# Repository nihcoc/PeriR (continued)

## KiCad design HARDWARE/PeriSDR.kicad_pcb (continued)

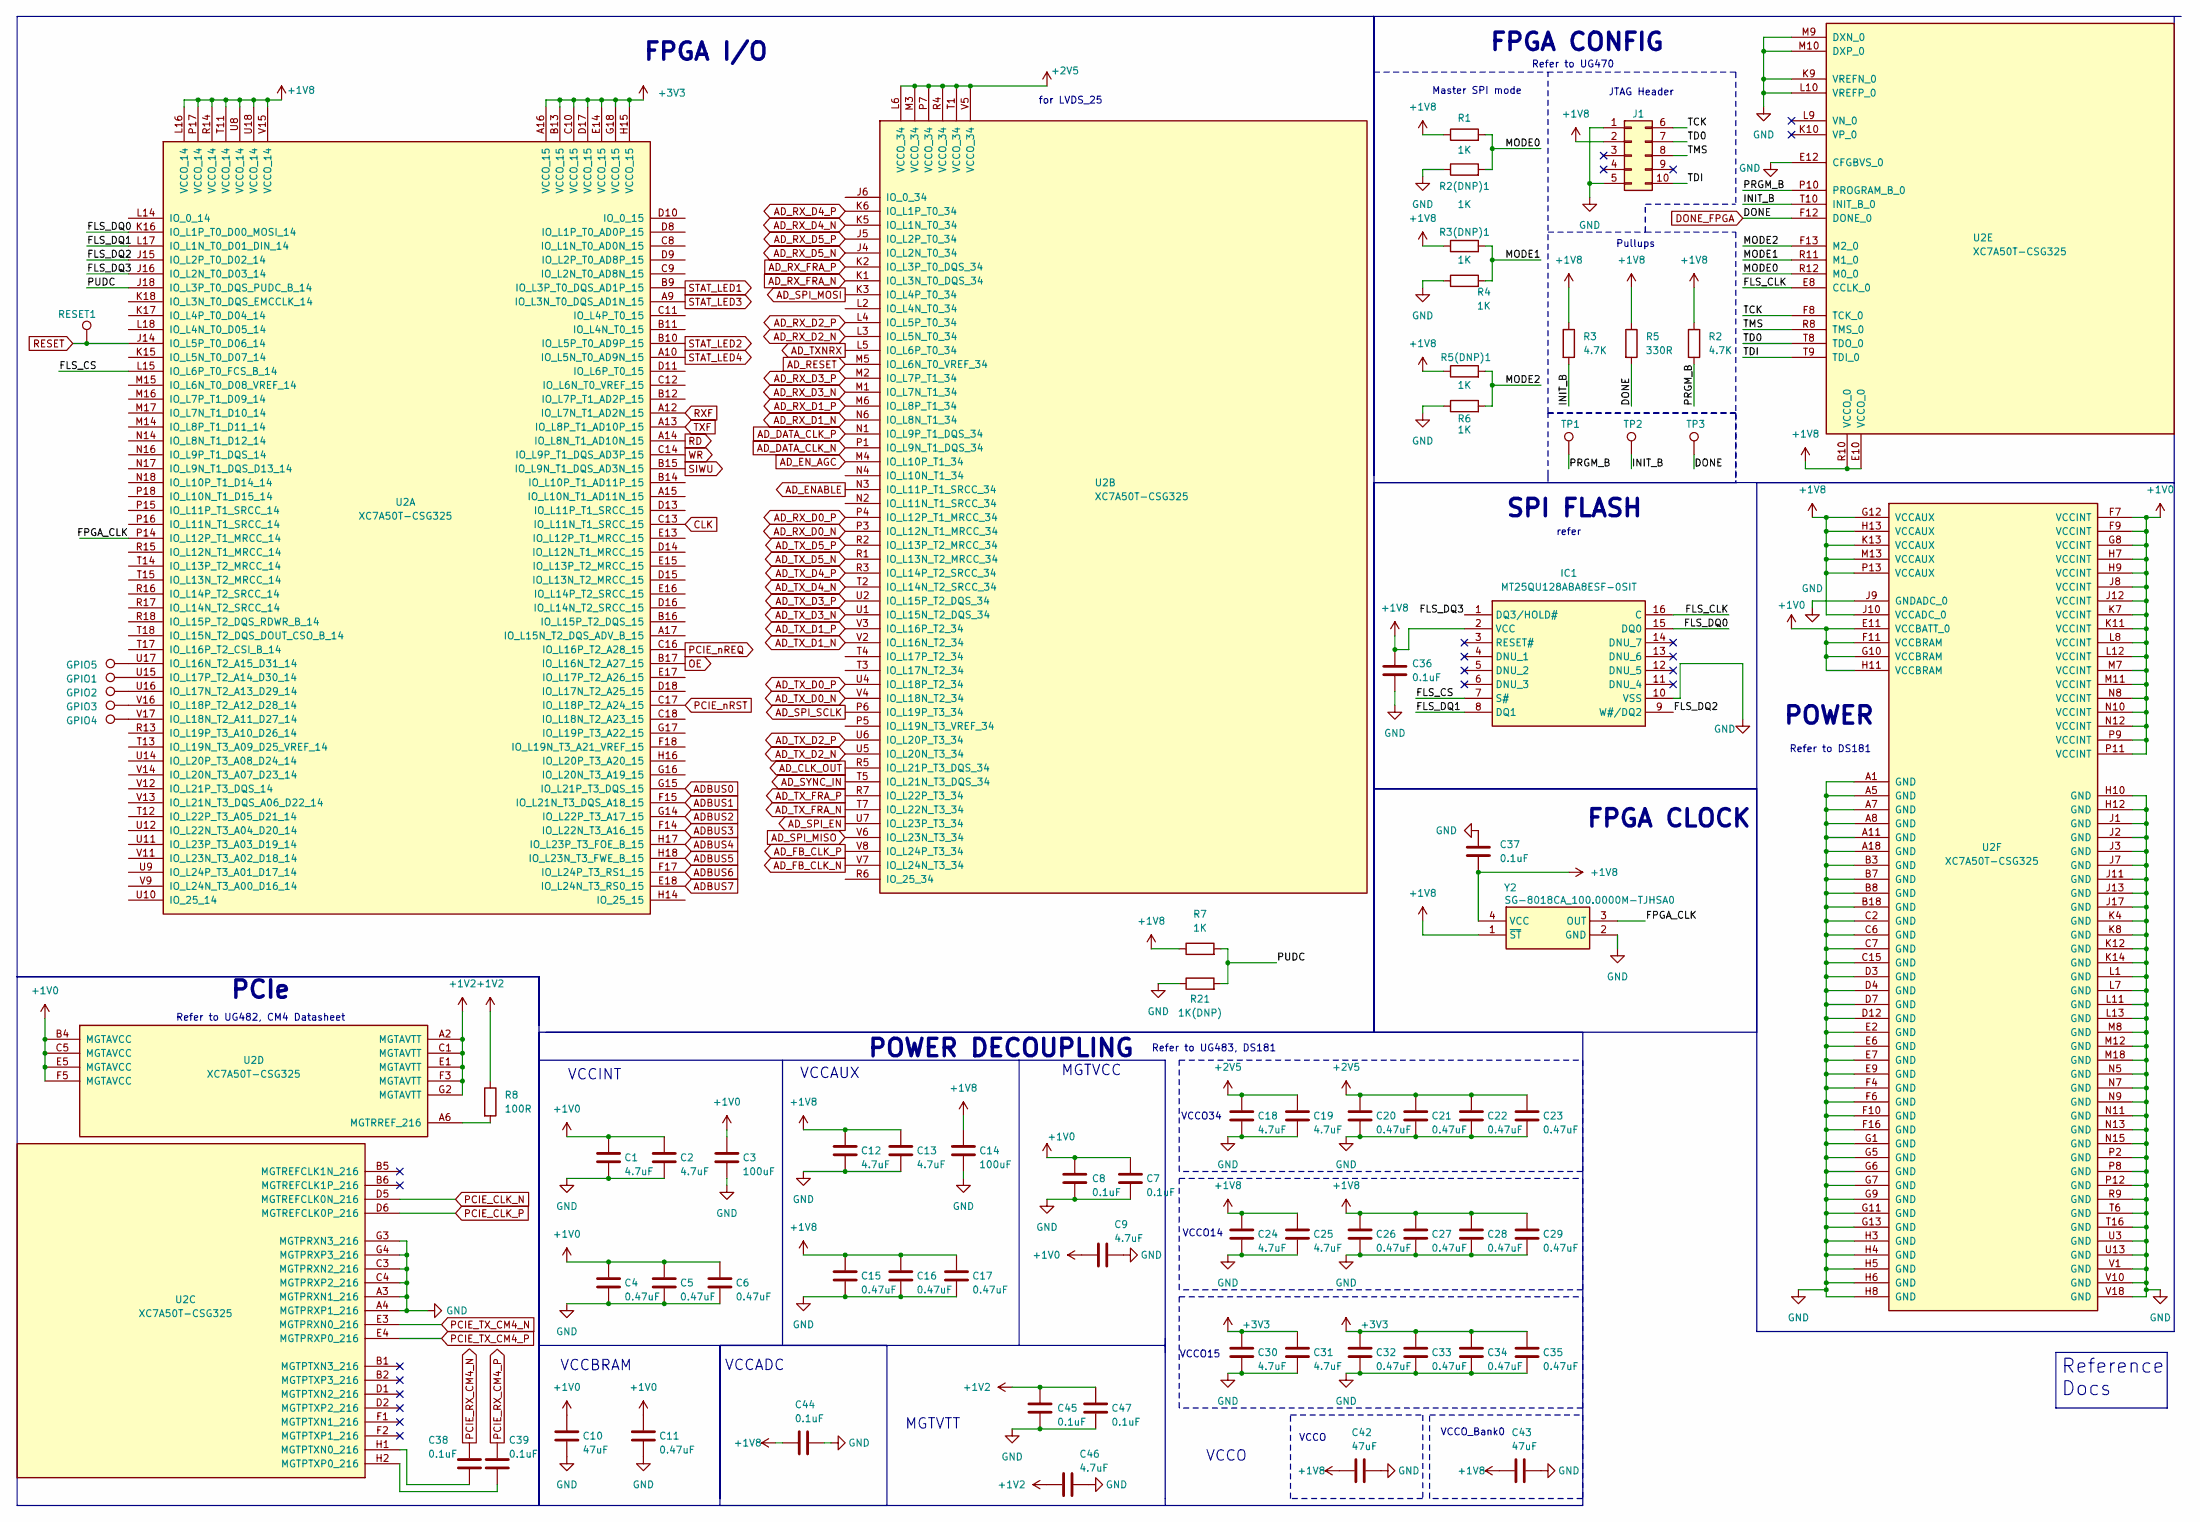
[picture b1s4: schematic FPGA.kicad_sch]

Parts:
C1, C2, C9, C12, C13, C18, C19, C24, C25, C30, C31, C46: 4.7uF; C_0402_1005Metric
C3, C14: 100uF; C_0805_2012Metric
C4, C5, C6, C11, C15, C16, C17, C20, C21, C22, C23, C26, C27, C28, C29, C32, C33, C34, C35: 0.47uF; C_0402_1005Metric
C7, C8, C36, C37, C38, C39, C44, C45, C47: 0.1uF; C_0402_1005Metric
C10, C42, C43: 47uF; C_0603_1608Metric
GPIO1, GPIO2, GPIO3, GPIO4, GPIO5: TestPoint; TestPoint_Pad_1.0x1.0mm
IC1: MT25QU128ABA8ESF-0SIT; SOIC127P1032X265-16N; Mouser Part Number 340-283176-TRAY
J1: Conn_02x05_Top_Bottom; PinHeader_2x05_P2.54mm_Vertical
R1, R2(DNP)1, R3(DNP)1, R4, R5(DNP)1, R6, R7: 1K; R_0402_1005Metric
R2, R3: 4.7K; R_0402_1005Metric
R5: 330R; R_0402_1005Metric
R8: 100R; R_0402_1005Metric
R21: 1K(DNP); R_0402_1005Metric
RESET1: TestPoint; TestPoint_Pad_1.0x1.0mm
TP1, TP2, TP3: TestPoint; TestPoint_Pad_1.0x1.0mm
U2: XC7A50T-CSG325; Xilinx_CSG325
Y2: SG-8018CA_100.0000M-TJHSA0; SG8018CA1000000MTJHSA0; Manufacturer_Part_Number SG-8018CA 100.0000M-TJHSA0

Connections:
+1V0: C1.1, C2.1, C3.1, C4.1, C5.1, C6.1, C7.1, C8.1, C9.1, C10.1, C11.1, U2.B4 (MGTAVCC), U2.C5 (MGTAVCC), U2.E5 (MGTAVCC), U2.E11 (VCCBATT_0), U2.F5 (MGTAVCC), U2.F7 (VCCINT), U2.F9 (VCCINT), U2.F11 (VCCBRAM), U2.G8 (VCCINT), U2.G10 (VCCBRAM), U2.H7 (VCCINT), U2.H9 (VCCINT), U2.H11 (VCCBRAM), U2.J8 (VCCINT), U2.J12 (VCCINT), U2.K7 (VCCINT), U2.K11 (VCCINT), U2.L8 (VCCINT), U2.L12 (VCCINT), U2.M7 (VCCINT), U2.M11 (VCCINT), U2.N8 (VCCINT), U2.N10 (VCCINT), U2.N12 (VCCINT), U2.P9 (VCCINT), U2.P11 (VCCINT); also elsewhere on the board
+1V2: C45.1, C46.1, C47.1, R8.1, U2.A2 (MGTAVTT), U2.C1 (MGTAVTT), U2.E1 (MGTAVTT), U2.F3 (MGTAVTT), U2.G2 (MGTAVTT); also elsewhere on the board
+1V8: C12.1, C13.1, C14.1, C15.1, C16.1, C17.1, C24.1, C25.1, C26.1, C27.1, C28.1, C29.1, C36.1, C37.1, C42.1, C43.1, C44.1, IC1.2 (VCC), J1.2, R1.1, R2.1, R3.1, R3(DNP)1.1, R5.1, R5(DNP)1.1, R7.1, U2.E10 (VCCO_0), U2.G12 (VCCAUX), U2.H13 (VCCAUX), U2.J10 (VCCADC_0), U2.K13 (VCCAUX), U2.L16 (VCCO_14), U2.M13 (VCCAUX), U2.P13 (VCCAUX), U2.P17 (VCCO_14), U2.R10 (VCCO_0), U2.R14 (VCCO_14), U2.T11 (VCCO_14), U2.U8 (VCCO_14), U2.U18 (VCCO_14), U2.V15 (VCCO_14), Y2.1 (~ST), Y2.4 (VCC); also elsewhere on the board
+2V5: C18.1, C19.1, C20.1, C21.1, C22.1, C23.1, U2.L6 (VCCO_34), U2.M3 (VCCO_34), U2.P7 (VCCO_34), U2.R4 (VCCO_34), U2.T1 (VCCO_34), U2.V5 (VCCO_34); also elsewhere on the board
+3V3: C30.1, C31.1, C32.1, C33.1, C34.1, C35.1, U2.A16 (VCCO_15), U2.B13 (VCCO_15), U2.C10 (VCCO_15), U2.D17 (VCCO_15), U2.E14 (VCCO_15), U2.G18 (VCCO_15), U2.H15 (VCCO_15); also elsewhere on the board
/FPGA/FLS_CLK: IC1.16 (C), U2.E8 (CCLK_0)
/FPGA/FLS_CS: IC1.7 (S#), U2.L15 (IO_L6P_T0_FCS_B_14)
/FPGA/FLS_DQ0: IC1.15 (DQ0), U2.K16 (IO_L1P_T0_D00_MOSI_14)
/FPGA/FLS_DQ1: IC1.8 (DQ1), U2.L17 (IO_L1N_T0_D01_DIN_14)
/FPGA/FLS_DQ2: IC1.9 (W#/DQ2), U2.J15 (IO_L2P_T0_D02_14)
/FPGA/FLS_DQ3: IC1.1 (DQ3/HOLD#), U2.J16 (IO_L2N_T0_D03_14)
/FPGA/FPGA_CLK: U2.P14 (IO_L12P_T1_MRCC_14), Y2.3 (OUT)
/FPGA/INIT_B: R3.2, TP2.1 (1_1), U2.T10 (INIT_B_0)
/FPGA/MODE0: R1.2, R2(DNP)1.2, U2.R12 (M0_0)
/FPGA/MODE1: R3(DNP)1.2, R4.2, U2.R11 (M1_0)
/FPGA/MODE2: R5(DNP)1.2, R6.2, U2.F13 (M2_0)
/FPGA/PRGM_B: R2.2, TP1.1 (1_1), U2.P10 (PROGRAM_B_0)
/FPGA/PUDC: R7.2, R21.2, U2.J18 (IO_L3P_T0_DQS_PUDC_B_14)
/FPGA/TCK: J1.6, U2.F8 (TCK_0)
/FPGA/TD0: J1.7, U2.T8 (TDO_0)
/FPGA/TDI: J1.10, U2.T9 (TDI_0)
/FPGA/TMS: J1.8, U2.R8 (TMS_0)
ADBUS0: U2.G15 (IO_L21P_T3_DQS_15); also elsewhere on the board
ADBUS1: U2.F15 (IO_L21N_T3_DQS_A18_15); also elsewhere on the board
ADBUS2: U2.G14 (IO_L22P_T3_A17_15); also elsewhere on the board
ADBUS3: U2.F14 (IO_L22N_T3_A16_15); also elsewhere on the board
ADBUS4: U2.H17 (IO_L23P_T3_FOE_B_15); also elsewhere on the board
ADBUS5: U2.H18 (IO_L23N_T3_FWE_B_15); also elsewhere on the board
ADBUS6: U2.F17 (IO_L24P_T3_RS1_15); also elsewhere on the board
ADBUS7: U2.E18 (IO_L24N_T3_RS0_15); also elsewhere on the board
AD_CLK_OUT: U2.R5 (IO_L21P_T3_DQS_34); also elsewhere on the board
AD_DATA_CLK_N: U2.P1 (IO_L9N_T1_DQS_34); also elsewhere on the board
AD_DATA_CLK_P: U2.N1 (IO_L9P_T1_DQS_34); also elsewhere on the board
AD_ENABLE: U2.N3 (IO_L11P_T1_SRCC_34); also elsewhere on the board
AD_EN_AGC: U2.M4 (IO_L10P_T1_34); also elsewhere on the board
AD_FB_CLK_N: U2.V7 (IO_L24N_T3_34); also elsewhere on the board
AD_FB_CLK_P: U2.V8 (IO_L24P_T3_34); also elsewhere on the board
AD_RESET: U2.M5 (IO_L6N_T0_VREF_34); also elsewhere on the board
AD_RX_D0_N: U2.P3 (IO_L12N_T1_MRCC_34); also elsewhere on the board
AD_RX_D0_P: U2.P4 (IO_L12P_T1_MRCC_34); also elsewhere on the board
AD_RX_D1_N: U2.N6 (IO_L8N_T1_34); also elsewhere on the board
AD_RX_D1_P: U2.M6 (IO_L8P_T1_34); also elsewhere on the board
AD_RX_D2_N: U2.L3 (IO_L5N_T0_34); also elsewhere on the board
AD_RX_D2_P: U2.L4 (IO_L5P_T0_34); also elsewhere on the board
AD_RX_D3_N: U2.M1 (IO_L7N_T1_34); also elsewhere on the board
AD_RX_D3_P: U2.M2 (IO_L7P_T1_34); also elsewhere on the board
AD_RX_D4_N: U2.K5 (IO_L1N_T0_34); also elsewhere on the board
AD_RX_D4_P: U2.K6 (IO_L1P_T0_34); also elsewhere on the board
AD_RX_D5_N: U2.J4 (IO_L2N_T0_34); also elsewhere on the board
AD_RX_D5_P: U2.J5 (IO_L2P_T0_34); also elsewhere on the board
AD_RX_FRA_N: U2.K1 (IO_L3N_T0_DQS_34); also elsewhere on the board
AD_RX_FRA_P: U2.K2 (IO_L3P_T0_DQS_34); also elsewhere on the board
AD_SPI_EN: U2.U7 (IO_L23P_T3_34); also elsewhere on the board
AD_SPI_MISO: U2.V6 (IO_L23N_T3_34); also elsewhere on the board
AD_SPI_MOSI: U2.K3 (IO_L4P_T0_34); also elsewhere on the board
AD_SPI_SCLK: U2.P6 (IO_L19P_T3_34); also elsewhere on the board
AD_SYNC_IN: U2.T5 (IO_L21N_T3_DQS_34); also elsewhere on the board
AD_TXNRX: U2.L5 (IO_L6P_T0_34); also elsewhere on the board
AD_TX_D0_N: U2.V4 (IO_L18N_T2_34); also elsewhere on the board
AD_TX_D0_P: U2.U4 (IO_L18P_T2_34); also elsewhere on the board
AD_TX_D1_N: U2.V2 (IO_L16N_T2_34); also elsewhere on the board
AD_TX_D1_P: U2.V3 (IO_L16P_T2_34); also elsewhere on the board
AD_TX_D2_N: U2.U5 (IO_L20N_T3_34); also elsewhere on the board
AD_TX_D2_P: U2.U6 (IO_L20P_T3_34); also elsewhere on the board
AD_TX_D3_N: U2.U1 (IO_L15N_T2_DQS_34); also elsewhere on the board
AD_TX_D3_P: U2.U2 (IO_L15P_T2_DQS_34); also elsewhere on the board
AD_TX_D4_N: U2.T2 (IO_L14N_T2_SRCC_34); also elsewhere on the board
AD_TX_D4_P: U2.R3 (IO_L14P_T2_SRCC_34); also elsewhere on the board
AD_TX_D5_N: U2.R1 (IO_L13N_T2_MRCC_34); also elsewhere on the board
AD_TX_D5_P: U2.R2 (IO_L13P_T2_MRCC_34); also elsewhere on the board
AD_TX_FRA_N: U2.T7 (IO_L22N_T3_34); also elsewhere on the board
AD_TX_FRA_P: U2.R7 (IO_L22P_T3_34); also elsewhere on the board
CLK: U2.C13 (IO_L11N_T1_SRCC_15); also elsewhere on the board
DONE_FPGA: R5.2, TP3.1 (1_1), U2.F12 (DONE_0); also elsewhere on the board
GND: C1.2, C2.2, C3.2, C4.2, C5.2, C6.2, C7.2, C8.2, C9.2, C10.2, C11.2, C12.2, C13.2, C14.2, C15.2, C16.2, C17.2, C18.2, C19.2, C20.2, C21.2, C22.2, C23.2, C24.2, C25.2, C26.2, C27.2, C28.2, C29.2, C30.2, C31.2, C32.2, C33.2, C34.2, C35.2, C36.2, C37.2, C42.2, C43.2, C44.2, C45.2, C46.2, C47.2, IC1.10 (VSS), J1.1, J1.5, R2(DNP)1.1, R4.1, R6.1, R21.1, U2.A1 (GND), U2.A3 (MGTPRXN1_216), U2.A4 (MGTPRXP1_216), U2.A5 (GND), U2.A7 (GND), U2.A8 (GND), U2.A11 (GND), U2.A18 (GND), U2.B3 (GND), U2.B7 (GND), U2.B8 (GND), U2.B18 (GND), U2.C2 (GND), U2.C3 (MGTPRXN2_216), U2.C4 (MGTPRXP2_216), U2.C6 (GND), U2.C7 (GND), U2.C15 (GND), U2.D3 (GND), U2.D4 (GND), U2.D7 (GND), U2.D12 (GND), U2.E2 (GND), U2.E6 (GND), U2.E7 (GND), U2.E9 (GND), U2.E12 (CFGBVS_0), U2.F4 (GND), U2.F6 (GND), U2.F10 (GND), U2.F16 (GND), U2.G1 (GND), U2.G3 (MGTPRXN3_216), U2.G4 (MGTPRXP3_216), U2.G5 (GND), U2.G6 (GND), U2.G7 (GND), U2.G9 (GND), U2.G11 (GND), U2.G13 (GND), U2.H3 (GND), U2.H4 (GND), U2.H5 (GND), U2.H6 (GND), U2.H8 (GND), U2.H10 (GND), U2.H12 (GND), U2.J1 (GND), U2.J2 (GND), U2.J3 (GND), U2.J7 (GND), U2.J9 (GNDADC_0), U2.J11 (GND), U2.J13 (GND), U2.J17 (GND), U2.K4 (GND), U2.K8 (GND), U2.K9 (VREFN_0), U2.K12 (GND), U2.K14 (GND), U2.L1 (GND), U2.L7 (GND), U2.L10 (VREFP_0), U2.L11 (GND), U2.L13 (GND), U2.M8 (GND), U2.M9 (DXN_0), U2.M10 (DXP_0), U2.M12 (GND), U2.M18 (GND), U2.N5 (GND), U2.N7 (GND), U2.N9 (GND), U2.N11 (GND), U2.N13 (GND), U2.N15 (GND), U2.P2 (GND), U2.P8 (GND), U2.P12 (GND), U2.R9 (GND), U2.T6 (GND), U2.T16 (GND), U2.U3 (GND), U2.U13 (GND), U2.V1 (GND), U2.V10 (GND), U2.V18 (GND), Y2.2 (GND); also elsewhere on the board
unnamed: GPIO5.1 (1_1), U2.U17 (IO_L16N_T2_A15_D31_14)
unnamed: GPIO2.1 (1_1), U2.U16 (IO_L17N_T2_A13_D29_14)
unnamed: GPIO1.1 (1_1), U2.U15 (IO_L17P_T2_A14_D30_14)
unnamed: GPIO4.1 (1_1), U2.V17 (IO_L18N_T2_A11_D27_14)
unnamed: GPIO3.1 (1_1), U2.V16 (IO_L18P_T2_A12_D28_14)
unnamed: C38.1, U2.H1 (MGTPTXN0_216)
unnamed: C39.1, U2.H2 (MGTPTXP0_216)
unnamed: R8.2, U2.A6 (MGTRREF_216)
OE: U2.B17 (IO_L16N_T2_A27_15); also elsewhere on the board
PCIE_CLK_N: U2.D5 (MGTREFCLK0N_216); also elsewhere on the board
PCIE_CLK_P: U2.D6 (MGTREFCLK0P_216); also elsewhere on the board
PCIE_RX_CM4_N: C38.2; also elsewhere on the board
PCIE_RX_CM4_P: C39.2; also elsewhere on the board
PCIE_TX_CM4_N: U2.E3 (MGTPRXN0_216); also elsewhere on the board
PCIE_TX_CM4_P: U2.E4 (MGTPRXP0_216); also elsewhere on the board
PCIE_nREQ: U2.C16 (IO_L16P_T2_A28_15); also elsewhere on the board
PCIE_nRST: U2.C17 (IO_L18P_T2_A24_15); also elsewhere on the board
RD: U2.A14 (IO_L8N_T1_AD10N_15); also elsewhere on the board
RESET: RESET1.1 (1_1), U2.J14 (IO_L5P_T0_D06_14)
RXF: U2.A12 (IO_L7N_T1_AD2N_15); also elsewhere on the board
SIWU: U2.B15 (IO_L9N_T1_DQS_AD3N_15); also elsewhere on the board
STAT_LED1: U2.B9 (IO_L3P_T0_DQS_AD1P_15); also elsewhere on the board
STAT_LED2: U2.B10 (IO_L5P_T0_AD9P_15); also elsewhere on the board
STAT_LED3: U2.A9 (IO_L3N_T0_DQS_AD1N_15); also elsewhere on the board
STAT_LED4: U2.A10 (IO_L5N_T0_AD9N_15); also elsewhere on the board
TXF: U2.A13 (IO_L8P_T1_AD10P_15); also elsewhere on the board
WR: U2.C14 (IO_L9P_T1_DQS_AD3P_15); also elsewhere on the board

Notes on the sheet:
VCCO34
Refer to UG470
VCCBRAM
POWER
FPGA CONFIG
FPGA CLOCK
PCIe
Refer to DS181
VCCO
VCCO
MGTVTT
for LVDS_25
Refer to UG482, CM4 Datasheet
VCCAUX
JTAG Header
MGTVCC
VCCINT
Pullups
VCCADC
Master SPI mode
FPGA I/O
POWER DECOUPLING
VCCO14
Refer to UG483, DS181
refer
SPI FLASH
VCCO15
VCCO_Bank0
Reference Docs

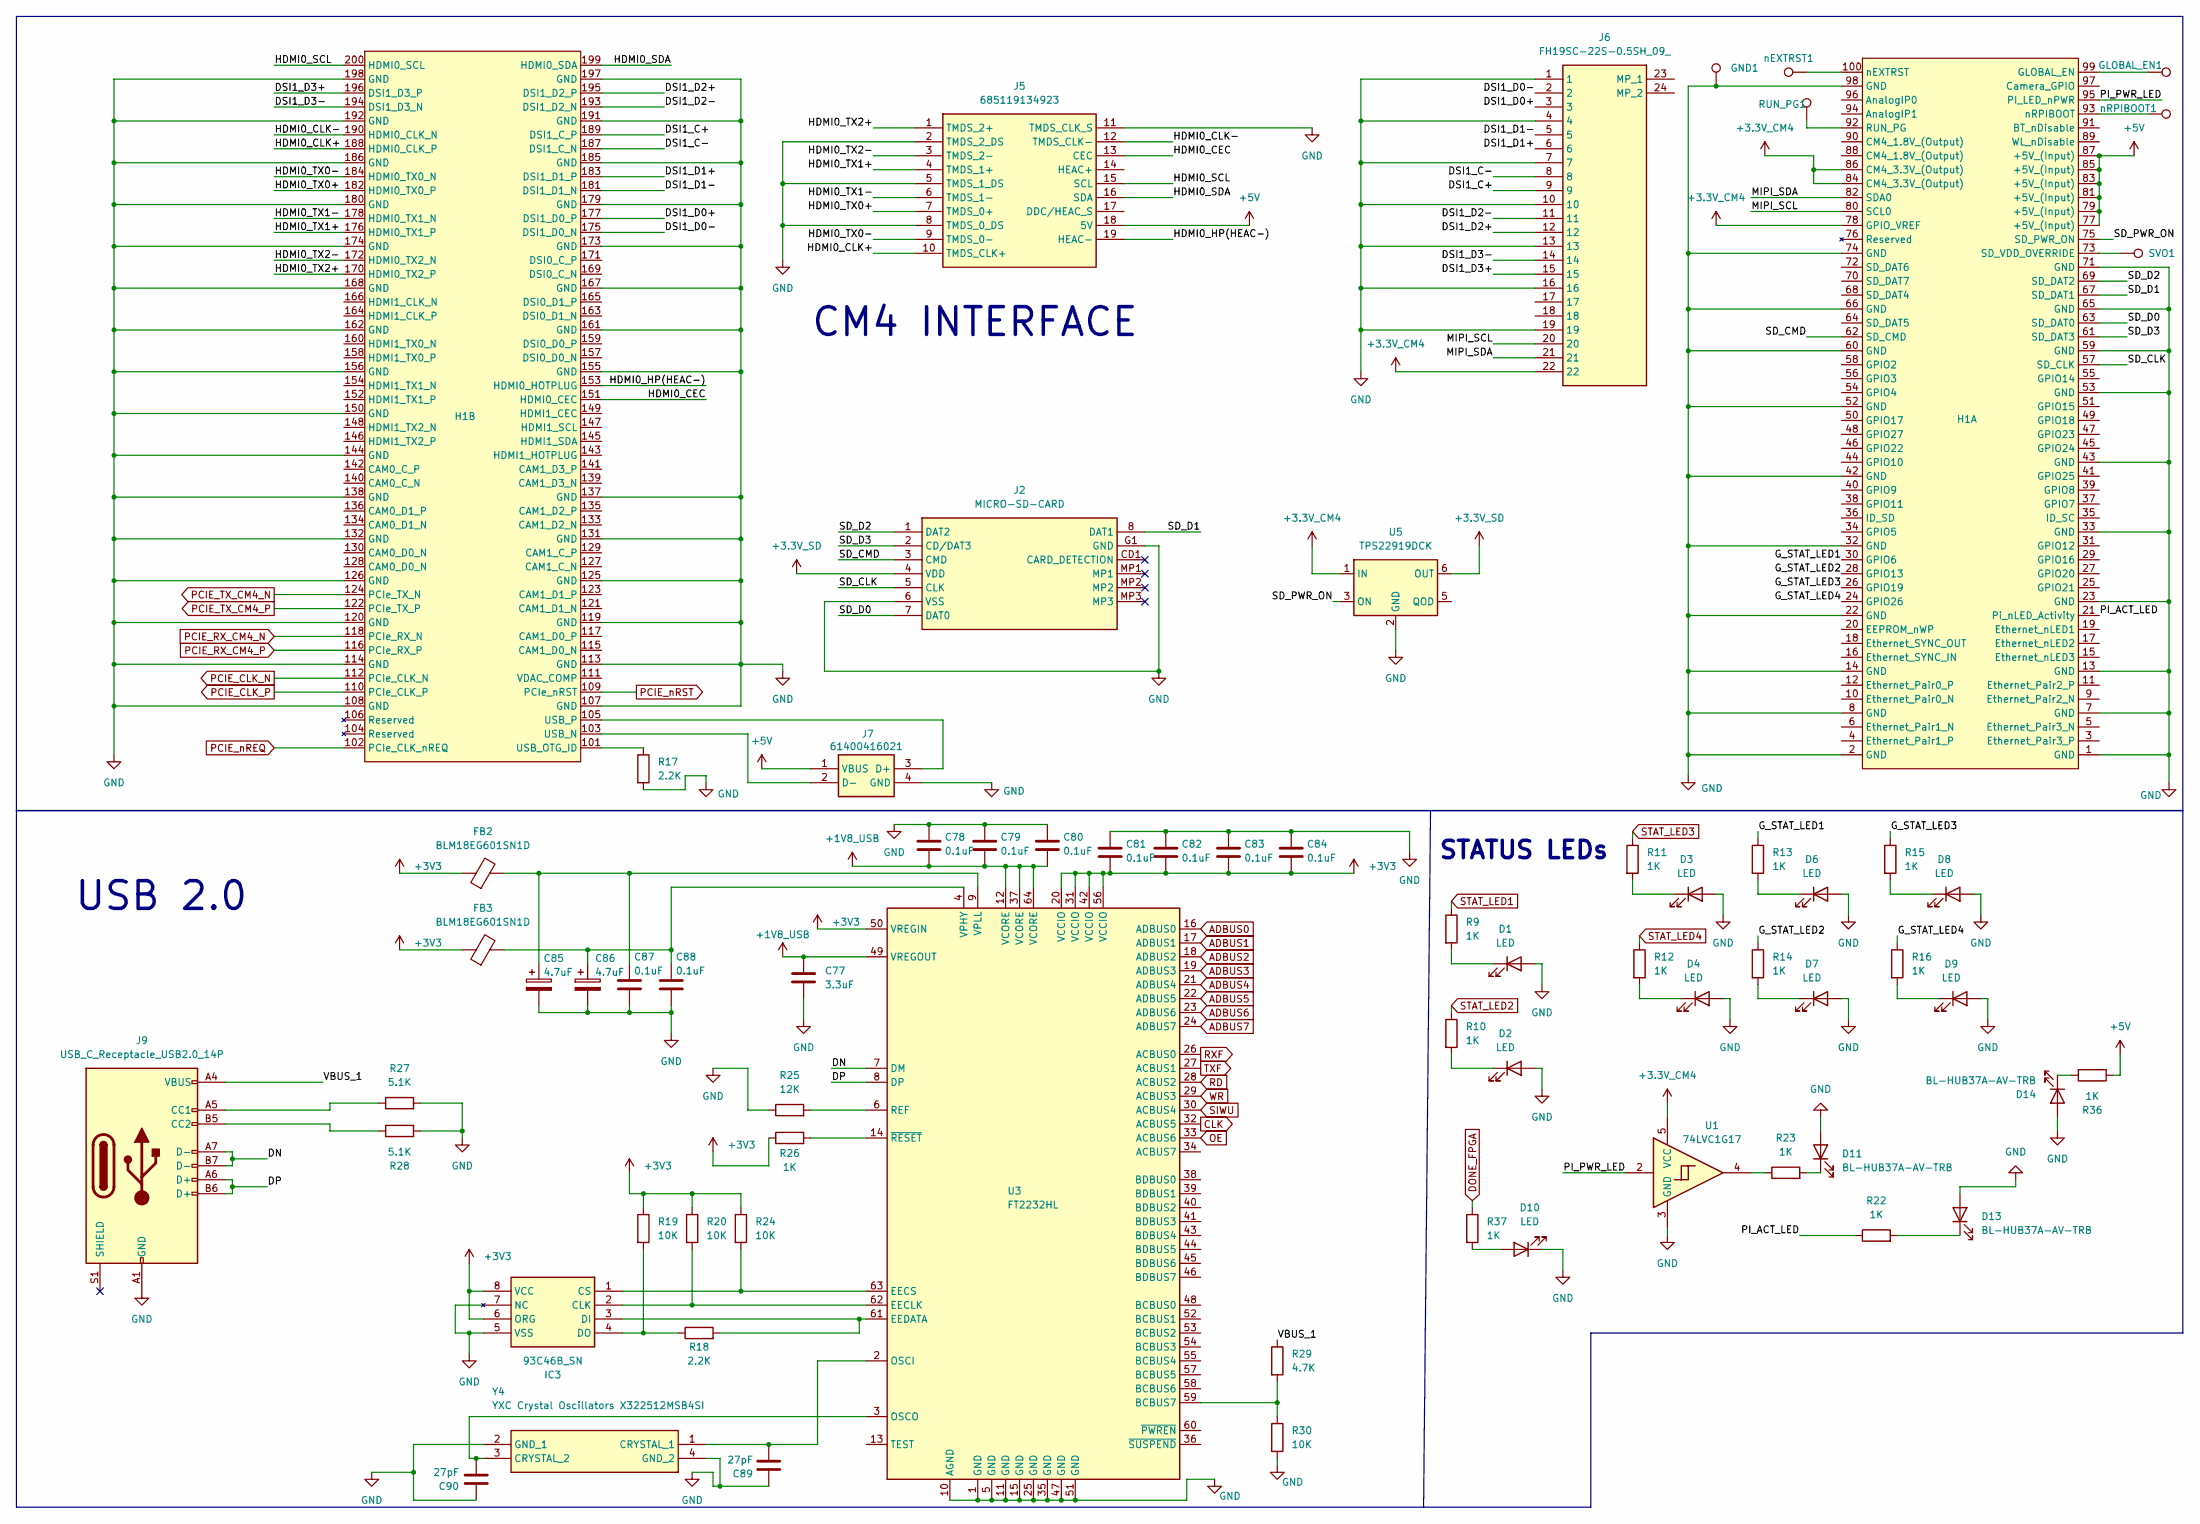
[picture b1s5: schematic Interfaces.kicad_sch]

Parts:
C77: 3.3uF; C_0603_1608Metric
C78, C79, C80, C81, C82, C83, C84, C87, C88: 0.1uF; C_0402_1005Metric
C85, C86: 4.7uF; C_0402_1005Metric
C89, C90: 27pF; C_0201_0603Metric
D1, D2, D3, D4, D6, D7, D8, D9, D10: LED; LED_0402_1005Metric
D11, D13, D14: BL-HUB37A-AV-TRB; LED_0402_1005Metric
FB2, FB3: BLM18EG601SN1D; L_0603_1608Metric
GLOBAL_EN1: TestPoint; TestPoint_Pad_1.0x1.0mm
GND1: TestPoint; TestPoint_Pad_1.0x1.0mm
H1: RaspberryPi-CM4-Module-Pad
IC3: 93C46B_SN; SOIC127P600X175-8N; Manufacturer_Part_Number 93C46B/SN; Mouser Part Number 579-93C46B/SN
J2: MICRO-SD-CARD; MICROSDCARD; Manufacturer_Part_Number MICRO-SD-CARD; Mouser Part Number N/A
J5: 685119134923; Mouser Part Number 710-685119134923
J6: FH19SC-22S-0.5SH_09_; FH19SC22S05SH09; Mouser Part Number 798-FH19SC22S05SH09
J7: 61400416021; USB-2.0-TYPE-A; Mouser Part Number 710-61400416021
J9: USB_C_Receptacle_USB2.0_14P; USB_C_Receptacle_JAE_DX07S016JA1R1500
R9, R10, R11, R12, R13, R14, R15, R16, R22, R23, R26, R36, R37: 1K; R_0402_1005Metric
R17, R18: 2.2K; R_0402_1005Metric
R19, R20, R24, R30: 10K; R_0402_1005Metric
R25: 12K; R_0402_1005Metric
R27, R28: 5.1K; R_0402_1005Metric
R29: 4.7K; R_0402_1005Metric
RUN_PG1: TestPoint; TestPoint_Pad_1.0x1.0mm
SVO1: TestPoint; TestPoint_Pad_1.0x1.0mm
U1: 74LVC1G17; SOT-23-5
U3: FT2232HL; LQFP-64_10x10mm_P0.5mm
U5: TPS22919DCK; SOT-363_SC-70-6
Y4: YXC Crystal Oscillators X322512MSB4SI; FA128400000MF20XK; Mouser Part Number 732-FA-12840MF20X-K
nEXTRST1: TestPoint; TestPoint_Pad_1.0x1.0mm
nRPIBOOT1: TestPoint; TestPoint_Pad_1.0x1.0mm

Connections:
+1V8_USB: C77.1, C78.2, C79.2, C80.2, U3.12 (VCORE), U3.37 (VCORE), U3.49 (VREGOUT), U3.64 (VCORE)
+3.3V_CM4: H1.78 (GPIO_VREF), H1.84 (CM4_3.3V_(Output)), H1.86 (CM4_3.3V_(Output)), J6.22, U1.5 (VCC), U5.1 (IN)
+3.3V_SD: J2.4 (VDD), U5.6 (OUT)
+3V3: C81.2, C82.2, C83.2, C84.2, FB2.1, FB3.1, IC3.6 (ORG), IC3.8 (VCC), R19.1, R20.1, R24.1, R26.1, U3.20 (VCCIO), U3.31 (VCCIO), U3.42 (VCCIO), U3.50 (VREGIN), U3.56 (VCCIO); also elsewhere on the board
+5V: H1.77 (+5V_(Input)), H1.79 (+5V_(Input)), H1.81 (+5V_(Input)), H1.83 (+5V_(Input)), H1.85 (+5V_(Input)), H1.87 (+5V_(Input)), J5.18 (5V), J7.1 (VBUS), R36.1; also elsewhere on the board
/Interfaces/DN: J9.A7 (D-), J9.B7 (D-), U3.7 (DM)
/Interfaces/DP: J9.A6 (D+), J9.B6 (D+), U3.8 (DP)
/Interfaces/DSI1_C+: H1.189 (DSI1_C_P), J6.9
/Interfaces/DSI1_C-: H1.187 (DSI1_C_N), J6.8
/Interfaces/DSI1_D0+: H1.177 (DSI1_D0_P), J6.3
/Interfaces/DSI1_D0-: H1.175 (DSI1_D0_N), J6.2
/Interfaces/DSI1_D1+: H1.183 (DSI1_D1_P), J6.6
/Interfaces/DSI1_D1-: H1.181 (DSI1_D1_N), J6.5
/Interfaces/DSI1_D2+: H1.195 (DSI1_D2_P), J6.12
/Interfaces/DSI1_D2-: H1.193 (DSI1_D2_N), J6.11
/Interfaces/DSI1_D3+: H1.196 (DSI1_D3_P), J6.15
/Interfaces/DSI1_D3-: H1.194 (DSI1_D3_N), J6.14
/Interfaces/G_STAT_LED1: H1.30 (GPIO6), R13.1
/Interfaces/G_STAT_LED2: H1.28 (GPIO13), R14.1
/Interfaces/G_STAT_LED3: H1.26 (GPIO19), R15.1
/Interfaces/G_STAT_LED4: H1.24 (GPIO26), R16.1
/Interfaces/HDMI0_CEC: H1.151 (HDMI0_CEC), J5.13 (CEC)
/Interfaces/HDMI0_CLK+: H1.188 (HDMI0_CLK_P), J5.10 (TMDS_CLK+)
/Interfaces/HDMI0_CLK-: H1.190 (HDMI0_CLK_N), J5.12 (TMDS_CLK-)
/Interfaces/HDMI0_HP(HEAC-): H1.153 (HDMI0_HOTPLUG), J5.19 (HEAC-)
/Interfaces/HDMI0_SCL: H1.200 (HDMI0_SCL), J5.15 (SCL)
/Interfaces/HDMI0_SDA: H1.199 (HDMI0_SDA), J5.16 (SDA)
/Interfaces/HDMI0_TX0+: H1.182 (HDMI0_TX0_P), J5.7 (TMDS_0+)
/Interfaces/HDMI0_TX0-: H1.184 (HDMI0_TX0_N), J5.9 (TMDS_0-)
/Interfaces/HDMI0_TX1+: H1.176 (HDMI0_TX1_P), J5.4 (TMDS_1+)
/Interfaces/HDMI0_TX1-: H1.178 (HDMI0_TX1_N), J5.6 (TMDS_1-)
/Interfaces/HDMI0_TX2+: H1.170 (HDMI0_TX2_P), J5.1 (TMDS_2+)
/Interfaces/HDMI0_TX2-: H1.172 (HDMI0_TX2_N), J5.3 (TMDS_2-)
/Interfaces/MIPI_SCL: H1.80 (SCL0), J6.20
/Interfaces/MIPI_SDA: H1.82 (SDA0), J6.21
/Interfaces/PI_ACT_LED: H1.21 (Pi_nLED_Activity), R22.1
/Interfaces/PI_PWR_LED: H1.95 (PI_LED_nPWR), U1.2
/Interfaces/SD_CLK: H1.57 (SD_CLK), J2.5 (CLK)
/Interfaces/SD_CMD: H1.62 (SD_CMD), J2.3 (CMD)
/Interfaces/SD_D0: H1.63 (SD_DAT0), J2.7 (DAT0)
/Interfaces/SD_D1: H1.67 (SD_DAT1), J2.8 (DAT1)
/Interfaces/SD_D2: H1.69 (SD_DAT2), J2.1 (DAT2)
/Interfaces/SD_D3: H1.61 (SD_DAT3), J2.2 (CD/DAT3)
/Interfaces/SD_PWR_ON: H1.75 (SD_PWR_ON), U5.3 (ON)
/Interfaces/VBUS_1: J9.A4 (VBUS), J9.A9 (VBUS), J9.B4 (VBUS), J9.B9 (VBUS), R29.1
ADBUS0: U3.16 (ADBUS0); also elsewhere on the board
ADBUS1: U3.17 (ADBUS1); also elsewhere on the board
ADBUS2: U3.18 (ADBUS2); also elsewhere on the board
ADBUS3: U3.19 (ADBUS3); also elsewhere on the board
ADBUS4: U3.21 (ADBUS4); also elsewhere on the board
ADBUS5: U3.22 (ADBUS5); also elsewhere on the board
ADBUS6: U3.23 (ADBUS6); also elsewhere on the board
ADBUS7: U3.24 (ADBUS7); also elsewhere on the board
CLK: U3.32 (ACBUS5); also elsewhere on the board
DONE_FPGA: R37.1; also elsewhere on the board
GND: C77.2, C78.1, C79.1, C80.1, C81.1, C82.1, C83.1, C84.1, C85.2, C86.2, C87.2, C88.2, C89.1, C90.1, D1.2 (A), D2.2 (A), D3.2 (A), D4.2 (A), D6.2 (A), D7.2 (A), D8.2 (A), D9.2 (A), D10.1 (K), D11.2 (A), D13.2 (A), D14.2 (A), GND1.1 (1_1), H1.1 (GND), H1.2 (GND), H1.7 (GND), H1.8 (GND), H1.13 (GND), H1.14 (GND), H1.22 (GND), H1.23 (GND), H1.32 (GND), H1.33 (GND), H1.42 (GND), H1.43 (GND), H1.52 (GND), H1.53 (GND), H1.59 (GND), H1.60 (GND), H1.65 (GND), H1.66 (GND), H1.71 (GND), H1.74 (GND), H1.98 (GND), H1.107 (GND), H1.108 (GND), H1.113 (GND), H1.114 (GND), H1.119 (GND), H1.120 (GND), H1.125 (GND), H1.126 (GND), H1.131 (GND), H1.132 (GND), H1.137 (GND), H1.138 (GND), H1.144 (GND), H1.150 (GND), H1.155 (GND), H1.156 (GND), H1.161 (GND), H1.162 (GND), H1.167 (GND), H1.168 (GND), H1.173 (GND), H1.174 (GND), H1.179 (GND), H1.180 (GND), H1.185 (GND), H1.186 (GND), H1.191 (GND), H1.192 (GND), H1.197 (GND), H1.198 (GND), IC3.5 (VSS), IC3.7 (NC), J2.6 (VSS), J2.G1 (GND), J5.2 (TMDS_2_DS), J5.5 (TMDS_1_DS), J5.8 (TMDS_0_DS), J5.11 (TMDS_CLK_S), J6.1, J6.4, J6.7, J6.10, J6.13, J6.16, J6.19, J7.4 (GND), J9.A1 (GND), J9.A12 (GND), J9.B1 (GND), J9.B12 (GND), R17.2, R25.1, R27.2, R28.2, R30.2, U1.3 (GND), U3.1 (GND), U3.5 (GND), U3.10 (AGND), U3.11 (GND), U3.15 (GND), U3.25 (GND), U3.35 (GND), U3.47 (GND), U3.51 (GND), U5.2 (GND), Y4.2 (GND_1), Y4.4 (GND_2); also elsewhere on the board
unnamed: D1.1 (K), R9.2
unnamed: D2.1 (K), R10.2
unnamed: D3.1 (K), R11.2
unnamed: D4.1 (K), R12.2
unnamed: D6.1 (K), R13.2
unnamed: D7.1 (K), R14.2
unnamed: D8.1 (K), R15.2
unnamed: D9.1 (K), R16.2
unnamed: D10.2 (A), R37.2
unnamed: D11.1 (K), R23.2
unnamed: D13.1 (K), R22.2
unnamed: D14.1 (K), R36.2
unnamed: GLOBAL_EN1.1 (1_1), H1.99 (GLOBAL_EN)
unnamed: H1.92 (RUN_PG), RUN_PG1.1 (1_1)
unnamed: H1.73 (SD_VDD_OVERRIDE), SVO1.1 (1_1)
unnamed: H1.100 (nEXTRST), nEXTRST1.1 (1_1)
unnamed: H1.93 (nRPIBOOT), nRPIBOOT1.1 (1_1)
unnamed: H1.103 (USB_N), J7.2 (D-)
unnamed: H1.101 (USB_OTG_ID), R17.1
unnamed: H1.105 (USB_P), J7.3 (D+)
unnamed: IC3.2 (CLK), R20.2, U3.62 (EECLK)
unnamed: IC3.1 (CS), R24.2, U3.63 (EECS)
unnamed: IC3.3 (DI), R18.2, U3.61 (EEDATA)
unnamed: IC3.4 (DO), R18.1, R19.2
unnamed: J9.A5 (CC1), R27.1
unnamed: J9.B5 (CC2), R28.1
unnamed: R23.1, U1.4
unnamed: R29.2, R30.1, U3.59 (BCBUS7)
unnamed: C89.2, U3.2 (OSCI), Y4.1 (CRYSTAL_1)
unnamed: C90.2, U3.3 (OSCO), Y4.3 (CRYSTAL_2)
unnamed: R25.2, U3.6 (REF)
unnamed: C86.1, C88.1, FB3.2, U3.4 (VPHY)
unnamed: C85.1, C87.1, FB2.2, U3.9 (VPLL)
unnamed: R26.2, U3.14 (~RESET)
OE: U3.33 (ACBUS6); also elsewhere on the board
PCIE_CLK_N: H1.112 (PCIe_CLK_N); also elsewhere on the board
PCIE_CLK_P: H1.110 (PCIe_CLK_P); also elsewhere on the board
PCIE_RX_CM4_N: H1.118 (PCIe_RX_N); also elsewhere on the board
PCIE_RX_CM4_P: H1.116 (PCIe_RX_P); also elsewhere on the board
PCIE_TX_CM4_N: H1.124 (PCIe_TX_N); also elsewhere on the board
PCIE_TX_CM4_P: H1.122 (PCIe_TX_P); also elsewhere on the board
PCIE_nREQ: H1.102 (PCIe_CLK_nREQ); also elsewhere on the board
PCIE_nRST: H1.109 (PCIe_nRST); also elsewhere on the board
RD: U3.28 (ACBUS2); also elsewhere on the board
RXF: U3.26 (ACBUS0); also elsewhere on the board
SIWU: U3.30 (ACBUS4); also elsewhere on the board
STAT_LED1: R9.1; also elsewhere on the board
STAT_LED2: R10.1; also elsewhere on the board
STAT_LED3: R11.1; also elsewhere on the board
STAT_LED4: R12.1; also elsewhere on the board
TXF: U3.27 (ACBUS1); also elsewhere on the board
WR: U3.29 (ACBUS3); also elsewhere on the board

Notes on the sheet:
CM4 INTERFACE
STATUS LEDs
USB 2.0
